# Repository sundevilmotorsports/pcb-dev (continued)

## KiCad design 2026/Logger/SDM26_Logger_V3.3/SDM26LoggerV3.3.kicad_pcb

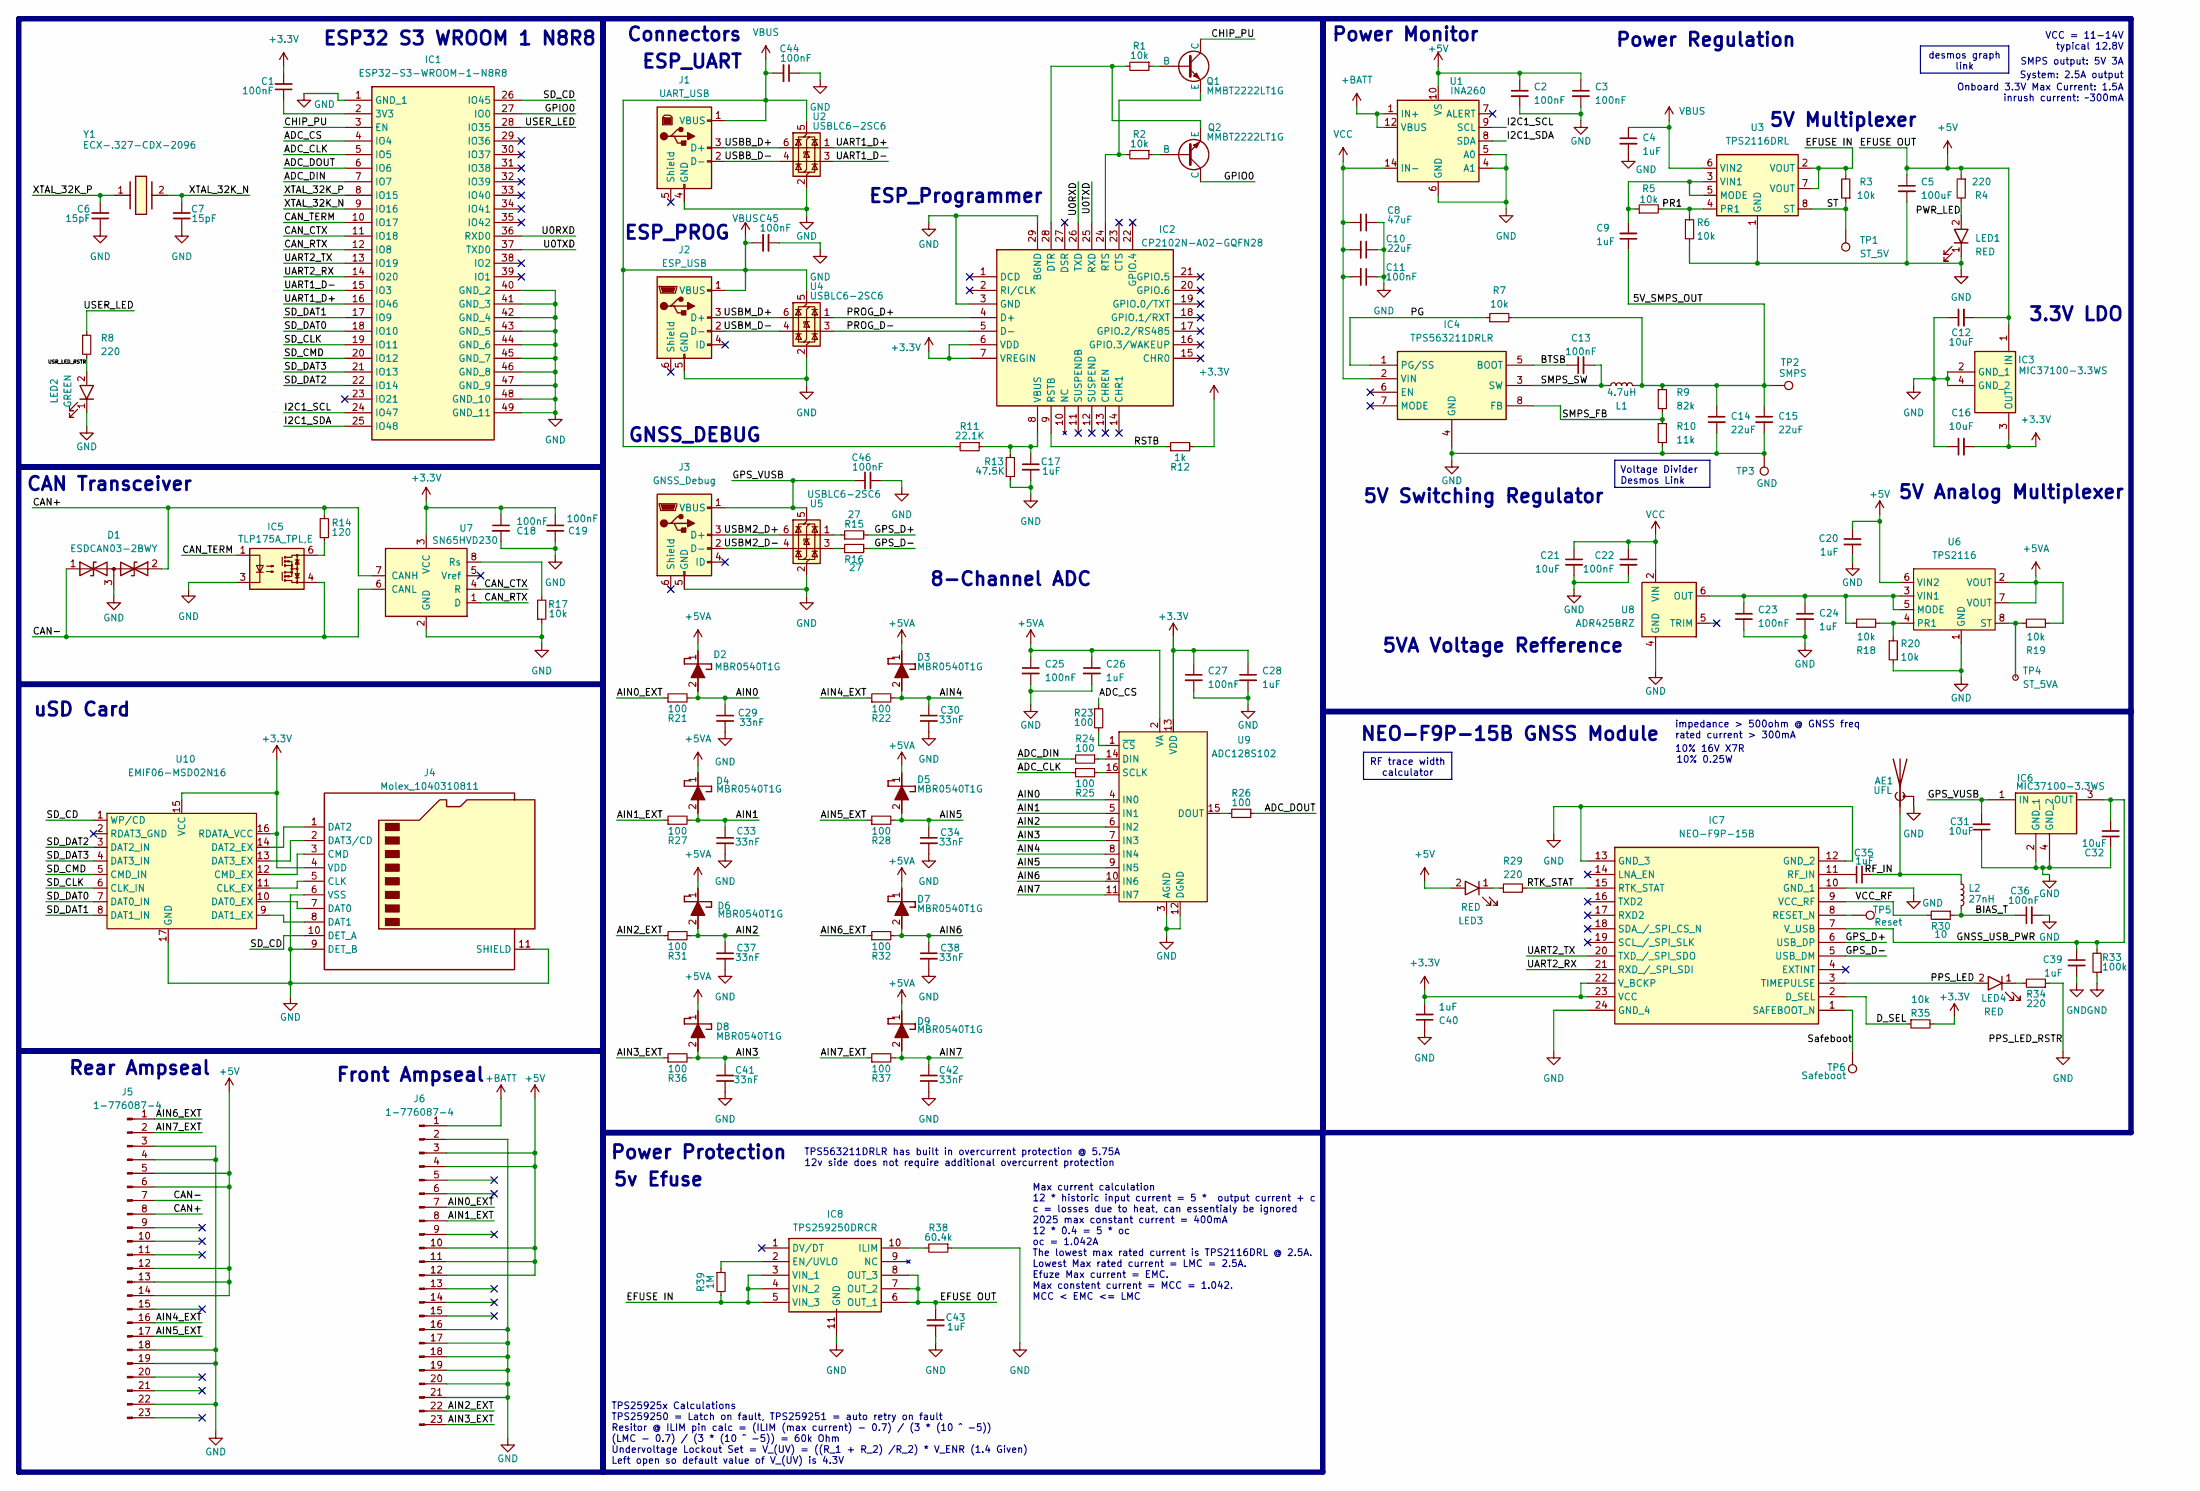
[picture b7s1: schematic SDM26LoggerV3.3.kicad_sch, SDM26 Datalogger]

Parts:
AE1: UFL; U.FL_Molex_MCRF_73412-0110_Vertical
C1, C2, C3, C11, C13, C18, C19, C22, C23, C25, C27, C36, C44, C45, C46: 100nF; C_0603_1608Metric
C4, C9, C17, C20, C24, C26, C28, C35, C39, C40, C43: 1uF; C_0603_1608Metric
C5: 100uF; CP_Elec_6.3x5.9
C6, C7: 15pF; C_0603_1608Metric
C8: 47uF; CP_Elec_6.3x5.9
C10, C14, C15: 22uF; C_0603_1608Metric
C12, C16, C21, C31, C32: 10uF; C_0603_1608Metric
C29, C30, C33, C34, C37, C38, C41, C42: 33nF; C_0603_1608Metric
D1: ESDCAN03-2BWY; SOT65P210X110-3N; Mouser Part Number 511-ESDCAN03-2BWY
D2, D3, D4, D5, D6, D7, D8, D9: MBR0540T1G; SOD3716X135N; Mouser Part Number 863-MBR0540T1G
IC1: ESP32-S3-WROOM-1-N8R8; ESP32S3WROOM1N8R8; Mouser Part Number 356-EP32S3WROOM1N8R8
IC2: CP2102N-A02-GQFN28; QFN50P500X500X80-29N-D; Mouser Part Number 634-CP2102NA02GQFN28
IC3, IC6: MIC37100-3.3WS; SOT230P700X180-4N; Mouser Part Number 998-MIC37100-3.3WS
IC4: TPS563211DRLR; SOTFL50P160X60-8N; Mouser Part Number 595-TPS563211DRLR
IC5: TLP175A_TPL,E; TLP266J; Mouser Part Number 757-TLP175A(TPLE
IC7: NEO-F9P-15B; NEOF9P15B; Mouser Part Number 377-NEO-F9P-15B
IC8: TPS259250DRCR; SON50P300X300X100-11L-D; Mouser Part Number 595-TPS259250DRCR
J1: UART_USB; 67068-7041
J2: ESP_USB; USB_Micro-B_Molex-105017-0001
J3: GNSS_Debug; USB_Micro-B_Molex-105017-0001
J4: Molex_1040310811; microSD_HC_Molex_104031-0811
J5, J6: 1-776087-4; CONN23_776087_TEC
L1: 4.7uH; L_Bourns_SRP7028A_7.3x6.6mm
L2: 27nH; L_0402_1005Metric
LED1, LED3, LED4: RED; SSFLXH100LID01; Mouser Part Number 696-SSFLXH100LID01
LED2: GREEN; SSFLXH100LID01; Mouser Part Number 696-SSFLXH100LID01
Q1, Q2: MMBT2222LT1G; SOT96P237X111-3N
R1, R2, R3, R5, R6, R7, R17, R18, R19, R20, R35: 10k; R_0603_1608Metric
R4, R8, R29, R34: 220; R_0603_1608Metric
R9: 82k; R_0603_1608Metric
R10: 11k; R_0603_1608Metric
R11: 22.1K; R_0603_1608Metric
R12: 1k; R_0603_1608Metric
R13: 47.5K; R_0603_1608Metric
R14: 120; R_0603_1608Metric
R15, R16: 27; R_0603_1608Metric
R21, R22, R23, R24, R25, R26, R27, R28, R31, R32, R36, R37: 100; R_0603_1608Metric
R30: 10; R_0603_1608Metric
R33: 100k; R_0603_1608Metric
R38: 60.4k; R_0603_1608Metric
R39: 1M; R_0603_1608Metric
TP1: ST_5V; TestPoint_Pad_1.5x1.5mm
TP2: SMPS; TestPoint_Pad_1.5x1.5mm
TP3: GND; TestPoint_Pad_1.5x1.5mm
TP4: ST_5VA; TestPoint_Pad_1.5x1.5mm
TP5: Reset; TestPoint_Pad_1.5x1.5mm
TP6: Safeboot; TestPoint_Pad_1.5x1.5mm
U1: INA260; TSSOP-16_4.4x5mm_P0.65mm
U2, U4, U5: USBLC6-2SC6; SOT-23-6
U3: TPS2116DRL; SOT-583-8
U6: TPS2116; SOT-5X3
U7: SN65HVD230; SOIC-8_3.9x4.9mm_P1.27mm
U8: ADR425BRZ; SOIC-8_3.9x4.9mm_P1.27mm
U9: ADC128S102; TSSOP-16_4.4x5mm_P0.65mm
U10: EMIF06-MSD02N16; UQFN-17-3.5x1.2mm
Y1: ECX-.327-CDX-2096; ECX327CDX2096; Mouser Part Number 520-X-.327-CDX2096

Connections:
+5V: C2.1, C3.1, C5.1, C12.2, C20.1, C43.1, IC3.1 (IN), IC8.6 (OUT_1), IC8.7 (OUT_2), IC8.8 (OUT_3), J5.5, J5.6, J5.12, J5.13, J5.14, J6.3, J6.4, J6.10, J6.11, J6.12, LED3.2 (A), R4.1, U1.10 (VS), U6.6 (VIN2)
+5VA: C25.1, C26.1, D2.1 (K), D3.1 (K), D4.1 (K), D5.1 (K), D6.1 (K), D7.1 (K), D8.1 (K), D9.1 (K), R19.2, U6.2 (VOUT), U6.7 (VOUT), U9.2 (VA)
+BATT: J6.1, U1.1 (IN+), U1.2 (IN+), U1.3 (IN+), U1.12 (VBUS)
/5V_SMPS_OUT: C9.1, C14.1, C15.1, L1.1, R7.2, R9.1, TP2.1
/ADC_CLK: IC1.5 (IO5), R25.1
/ADC_CS: IC1.4 (IO4), R23.1
/ADC_DIN: IC1.7 (IO7), R24.2
/ADC_DOUT: IC1.6 (IO6), R26.1
/AIN0: C29.1, D2.2 (A), R21.2, U9.4 (IN0)
/AIN0_EXT: J6.7, R21.1
/AIN1: C33.1, D4.2 (A), R27.2, U9.5 (IN1)
/AIN1_EXT: J6.8, R27.1
/AIN2: C37.1, D6.2 (A), R31.2, U9.6 (IN2)
/AIN2_EXT: J6.22, R31.1
/AIN3: C41.1, D8.2 (A), R36.2, U9.7 (IN3)
/AIN3_EXT: J6.23, R36.1
/AIN4: C30.1, D3.2 (A), R22.2, U9.8 (IN4)
/AIN4_EXT: J5.16, R22.1
/AIN5: C34.1, D5.2 (A), R28.2, U9.9 (IN5)
/AIN5_EXT: J5.17, R28.1
/AIN6: C38.1, D7.2 (A), R32.2, U9.10 (IN6)
/AIN6_EXT: J5.1, R32.1
/AIN7: C42.1, D9.2 (A), R37.2, U9.11 (IN7)
/AIN7_EXT: J5.2, R37.1
/BIAS_T: C36.1, L2.2, R30.1
/BTSB: C13.1, IC4.5 (BOOT)
/CAN+: D1.2, J5.8, R14.2, U7.7 (CANH)
/CAN-: D1.1, IC5.4, J5.7, U7.6 (CANL)
/CAN_CTX: IC1.11 (IO18), U7.4 (R)
/CAN_RTX: IC1.12 (IO8), U7.1 (D)
/CAN_TERM: IC1.10 (IO17), IC5.1
/CHIP_PU: IC1.3 (EN), Q1.1 (C)
/D_SEL: IC7.2 (D_SEL), R35.1
/EFUSE IN: IC8.3 (VIN_1), IC8.4 (VIN_2), IC8.5 (VIN_3), R3.2, R39.2, U3.2 (VOUT), U3.7 (VOUT)
/GNSS_USB_PWR: C32.1, C39.1, IC6.3 (OUT), IC7.7 (V_USB), R33.2
/GPIO0: IC1.27 (IO0), Q2.1 (C)
/GPS_D+: IC7.6 (USB_DP), R15.2
/GPS_D-: IC7.5 (USB_DM), R16.1
/GPS_VUSB: C31.2, C46.2, IC6.1 (IN), J3.1 (VBUS), U5.5 (VBUS)
/I2C1_SCL: IC1.24 (IO47), U1.9 (SCL)
/I2C1_SDA: IC1.25 (IO48), U1.8 (SDA)
/PG: IC4.1 (PG/SS), R7.1
/PPS_LED: IC7.3 (TIMEPULSE), LED4.2 (A)
/PR1: R5.2, R6.1, U3.4 (PR1)
/PROG_D+: IC2.4 (D+), U4.1 (I/O1)
/PROG_D-: IC2.5 (D-), U4.3 (I/O2)
/PWR_LED: LED1.2 (A), R4.2
/RF_IN: AE1.1 (A), C35.2, L2.1
/RSTB: IC2.9 (RSTB), R12.1
/RTK_STAT: IC7.15 (RTK_STAT), R29.2
/SD_CD: IC1.26 (IO45), J4.10 (DET_A), U10.1 (WP/CD)
/SD_CLK: IC1.19 (IO11), U10.6 (CLK_IN)
/SD_CMD: IC1.20 (IO12), U10.5 (CMD_IN)
/SD_DAT0: IC1.18 (IO10), U10.7 (DAT0_IN)
/SD_DAT1: IC1.17 (IO9), U10.8 (DAT1_IN)
/SD_DAT2: IC1.22 (IO14), U10.3 (DAT2_IN)
/SD_DAT3: IC1.21 (IO13), U10.4 (DAT3_IN)
/SMPS_FB: IC4.8 (FB), R9.2, R10.1
/SMPS_SW: C13.2, IC4.3 (SW), L1.2
/ST: R3.1, TP1.1, U3.8 (ST)
/Safeboot: IC7.1 (SAFEBOOT_N), TP6.1
/U0RXD: IC1.36 (RXD0), IC2.26 (TXD)
/U0TXD: IC1.37 (TXD0), IC2.25 (RXD)
/UART1_D+: IC1.16 (IO46), U2.1 (I/O1)
/UART1_D-: IC1.15 (IO3), U2.3 (I/O2)
/UART2_RX: IC1.14 (IO20), IC7.21 (RXD_/_SPI_SDI)
/UART2_TX: IC1.13 (IO19), IC7.20 (TXD_/_SPI_SDO)
/USBB_D+: J1.3 (D+), U2.6 (I/O1)
/USBB_D-: J1.2 (D-), U2.4 (I/O2)
/USBM2_D+: J3.3 (D+), U5.6 (I/O1)
/USBM2_D-: J3.2 (D-), U5.4 (I/O2)
/USBM_D+: J2.3 (D+), U4.6 (I/O1)
/USBM_D-: J2.2 (D-), U4.4 (I/O2)
/USER_LED: IC1.28 (IO35), R8.1
/USR_LED_RSTR: LED2.2 (A), R8.2
/VCC_RF: IC7.9 (VCC_RF), R30.2
/XTAL_32K_N: C7.2, IC1.9 (IO16), Y1.2
/XTAL_32K_P: C6.2, IC1.8 (IO15), Y1.1
GND: AE1.2 (Shield), C2.2, C3.2, C4.2, C5.2, C6.1, C7.1, C8.1, C10.1, C11.1, C12.1, C14.2, C15.2, C16.1, C17.2, C18.2, C19.2, C20.2, C21.2, C22.2, C23.2, C24.2, C25.2, C26.2, C27.2, C28.2, C29.2, C30.2, C31.1, C32.2, C33.2, C34.2, C36.2, C37.2, C38.2, C39.2, C40.1, C41.2, C42.2, C43.2, C44.1, C45.1, C46.1, D1.3, IC1.1 (GND_1), IC1.40 (GND_2), IC1.41 (GND_3), IC1.42 (GND_4), IC1.43 (GND_5), IC1.44 (GND_6), IC1.45 (GND_7), IC1.46 (GND_8), IC1.47 (GND_9), IC1.48 (GND_10), IC1.49 (GND_11), IC2.3 (GND), IC2.29 (BGND), IC3.2 (GND_1), IC3.4 (GND_2), IC4.4 (GND), IC5.3, IC6.2 (GND_1), IC6.4 (GND_2), IC7.10 (GND_1), IC7.12 (GND_2), IC7.13 (GND_3), IC7.24 (GND_4), IC8.11 (GND), J1.4 (GND), J2.5 (GND), J3.5 (GND), J4.6 (VSS), J4.9 (DET_B), J4.11 (SHIELD), J5.3, J5.4, J5.18, J5.19, J5.22, J6.2, J6.16, J6.17, J6.18, J6.19, J6.20, J6.21, LED1.1 (K), LED2.1 (K), R6.2, R10.2, R13.2, R17.1, R20.2, R33.1, R34.1, R38.1, TP3.1, U1.4 (A1), U1.5 (A0), U1.6 (GND), U1.11 (GND), U2.2 (GND), U3.1 (GND), U4.2 (GND), U5.2 (GND), U6.1 (GND), U7.2 (GND), U8.4 (GND), U9.3 (AGND), U9.12 (DGND), U10.17 (GND)
unnamed: IC2.28 (DTR), Q2.3 (E), R1.2
unnamed: IC2.24 (RTS), Q1.3 (E), R2.2
unnamed: C17.1, IC2.8 (VBUS), R11.1, R13.1
unnamed: IC5.6, R14.1
unnamed: IC7.8 (RESET_N), TP5.1
unnamed: C35.1, IC7.11 (RF_IN)
unnamed: IC8.2 (EN/UVLO), R39.1
unnamed: IC8.10 (ILIM), R38.2
unnamed: J4.5 (CLK), U10.11 (CLK_EX)
unnamed: J4.3 (CMD), U10.12 (CMD_EX)
unnamed: J4.7 (DAT0), U10.10 (DAT0_EX)
unnamed: J4.8 (DAT1), U10.9 (DAT1_EX)
unnamed: J4.1 (DAT2), U10.14 (DAT2_EX)
unnamed: J4.2 (DAT3/CD), U10.13 (DAT3_EX)
unnamed: LED3.1 (K), R29.1
unnamed: LED4.1 (K), R34.2
unnamed: Q1.2 (B), R1.1
unnamed: Q2.2 (B), R2.1
unnamed: R15.1, U5.1 (I/O1)
unnamed: R16.2, U5.3 (I/O2)
unnamed: C9.2, R5.1, U3.3 (VIN1), U3.5 (MODE)
unnamed: C23.1, C24.1, R18.1, U6.3 (VIN1), U6.5 (MODE), U8.6 (OUT)
unnamed: R18.2, R20.1, U6.4 (PR1)
unnamed: R19.1, TP4.1, U6.8 (ST)
unnamed: R17.2, U7.8 (Rs)
unnamed: R24.1, U9.14 (DIN)
unnamed: R26.2, U9.15 (DOUT)
unnamed: R25.2, U9.16 (SCLK)
unnamed: R23.2, U9.1 (~CS)
VBUS: C4.1, C44.2, C45.2, J1.1 (VBUS), J2.1 (VBUS), R11.2, U2.5 (VBUS), U3.6 (VIN2), U4.5 (VBUS)
VCC: C8.2, C10.2, C11.2, C21.1, C22.1, IC4.2 (VIN), U1.14 (IN-), U1.15 (IN-), U1.16 (IN-), U8.2 (VIN)

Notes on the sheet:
Power Regulation
5V Multiplexer
CAN Transceiver
10% 16V X7R
5v Efuse
inrush current: ~300mA
5V Switching Regulator
5V Analog Multiplexer
ESP32 S3 WROOM 1 N8R8
Power Monitor
Connectors
10% 0.25W
ESP_PROG
Onboard 3.3V Max Current: 1.5A
impedance > 500ohm @ GNSS freq rated current > 300mA
Front Ampseal
3.3V LDO
VCC = 11-14V typical 12.8V
GNSS_DEBUG
Max current calculation 12 * historic input current = 5 * output current + c c = losses due to heat, can essentialy be ignored 2025 max constant current = 400mA 12 * 0.4 = 5 * oc oc = 1.042A The lowest max rated current is TPS2116DRL @ 2.5A. Lowest Max rated current = LMC = 2.5A. Efuze Max current 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
ESP_UART
TPS563211DRLR has built in overcurrent protection @ 5.75A 12v side does not require additional overcurrent protection
8-Channel ADC
uSD Card
ESP_Programmer
Power Protection
5VA Voltage Refference
SMPS output: 5V 3A
NEO-F9P-15B GNSS Module
System: 2.5A output
Rear Ampseal
TPS25925x Calculations TPS259250 = Latch on fault, TPS259251 = auto retry on fault Resitor @ ILIM pin calc = (ILIM (max current) - 0.7) / (3 * (10 ^ -5)) (LMC - 0.7) / (3 * (10 ^ -5)) = 60k Ohm Undervoltage Lockout Set = V_(UV) = ((R_1 + R_2) /R_2) * V_ENR (1.4 Given) Left open so default value of 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
desmos graph link
Voltage Divider Desmos Link
RF trace width calculator

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
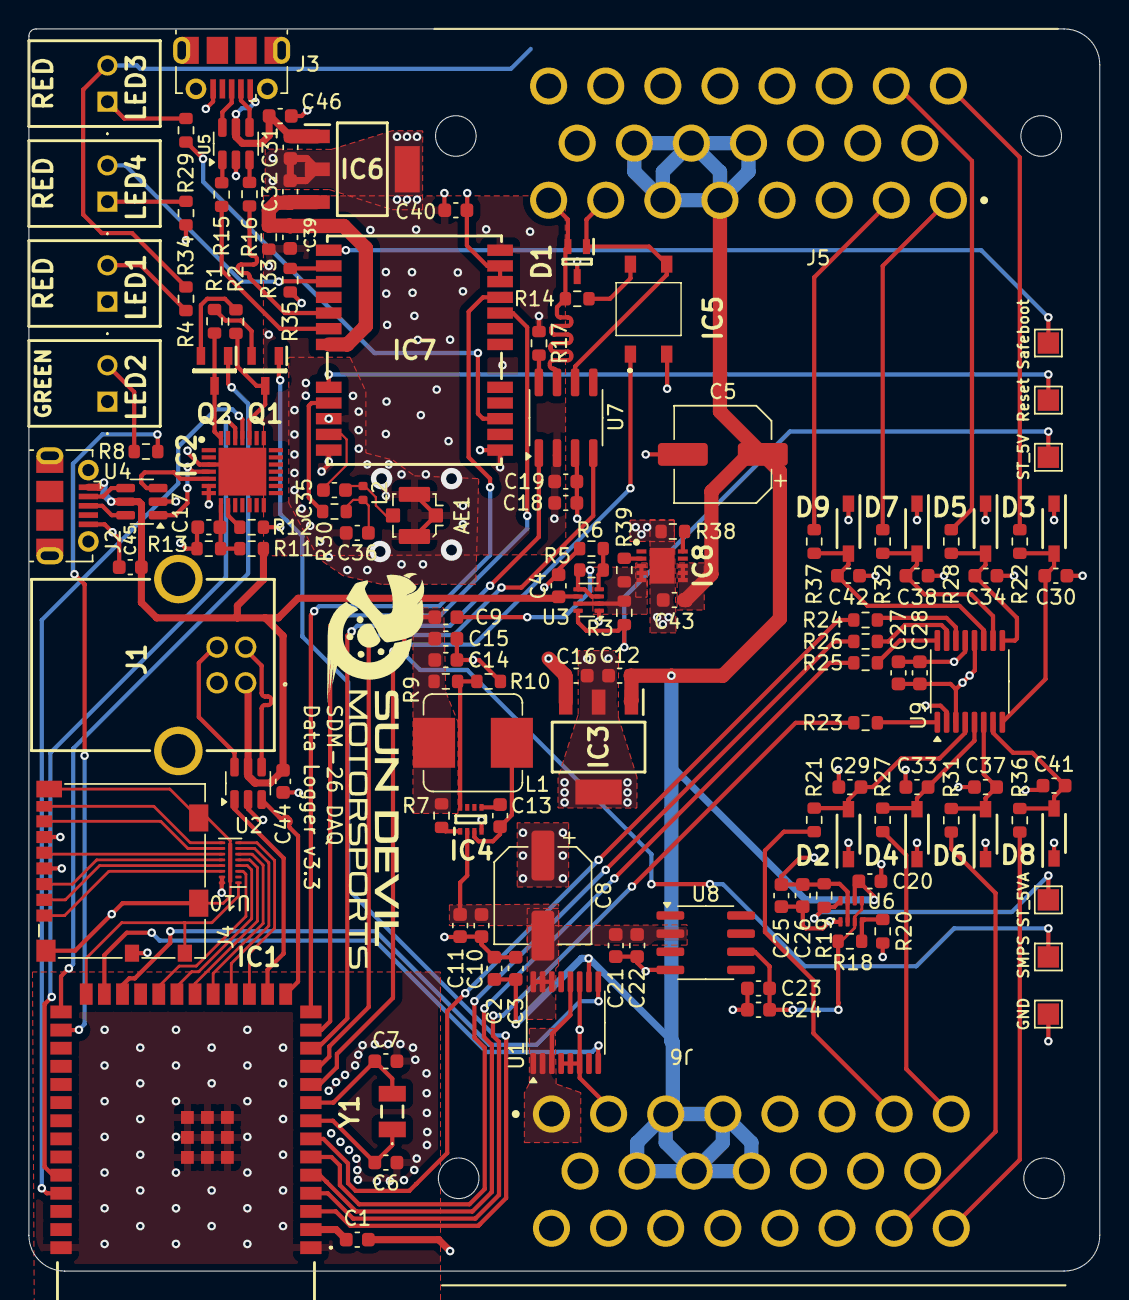
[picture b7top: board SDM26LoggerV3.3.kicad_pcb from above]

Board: 4 copper layers, 75.0 x 87.0 mm, 134 parts (0 on the bottom side), 112 nets.

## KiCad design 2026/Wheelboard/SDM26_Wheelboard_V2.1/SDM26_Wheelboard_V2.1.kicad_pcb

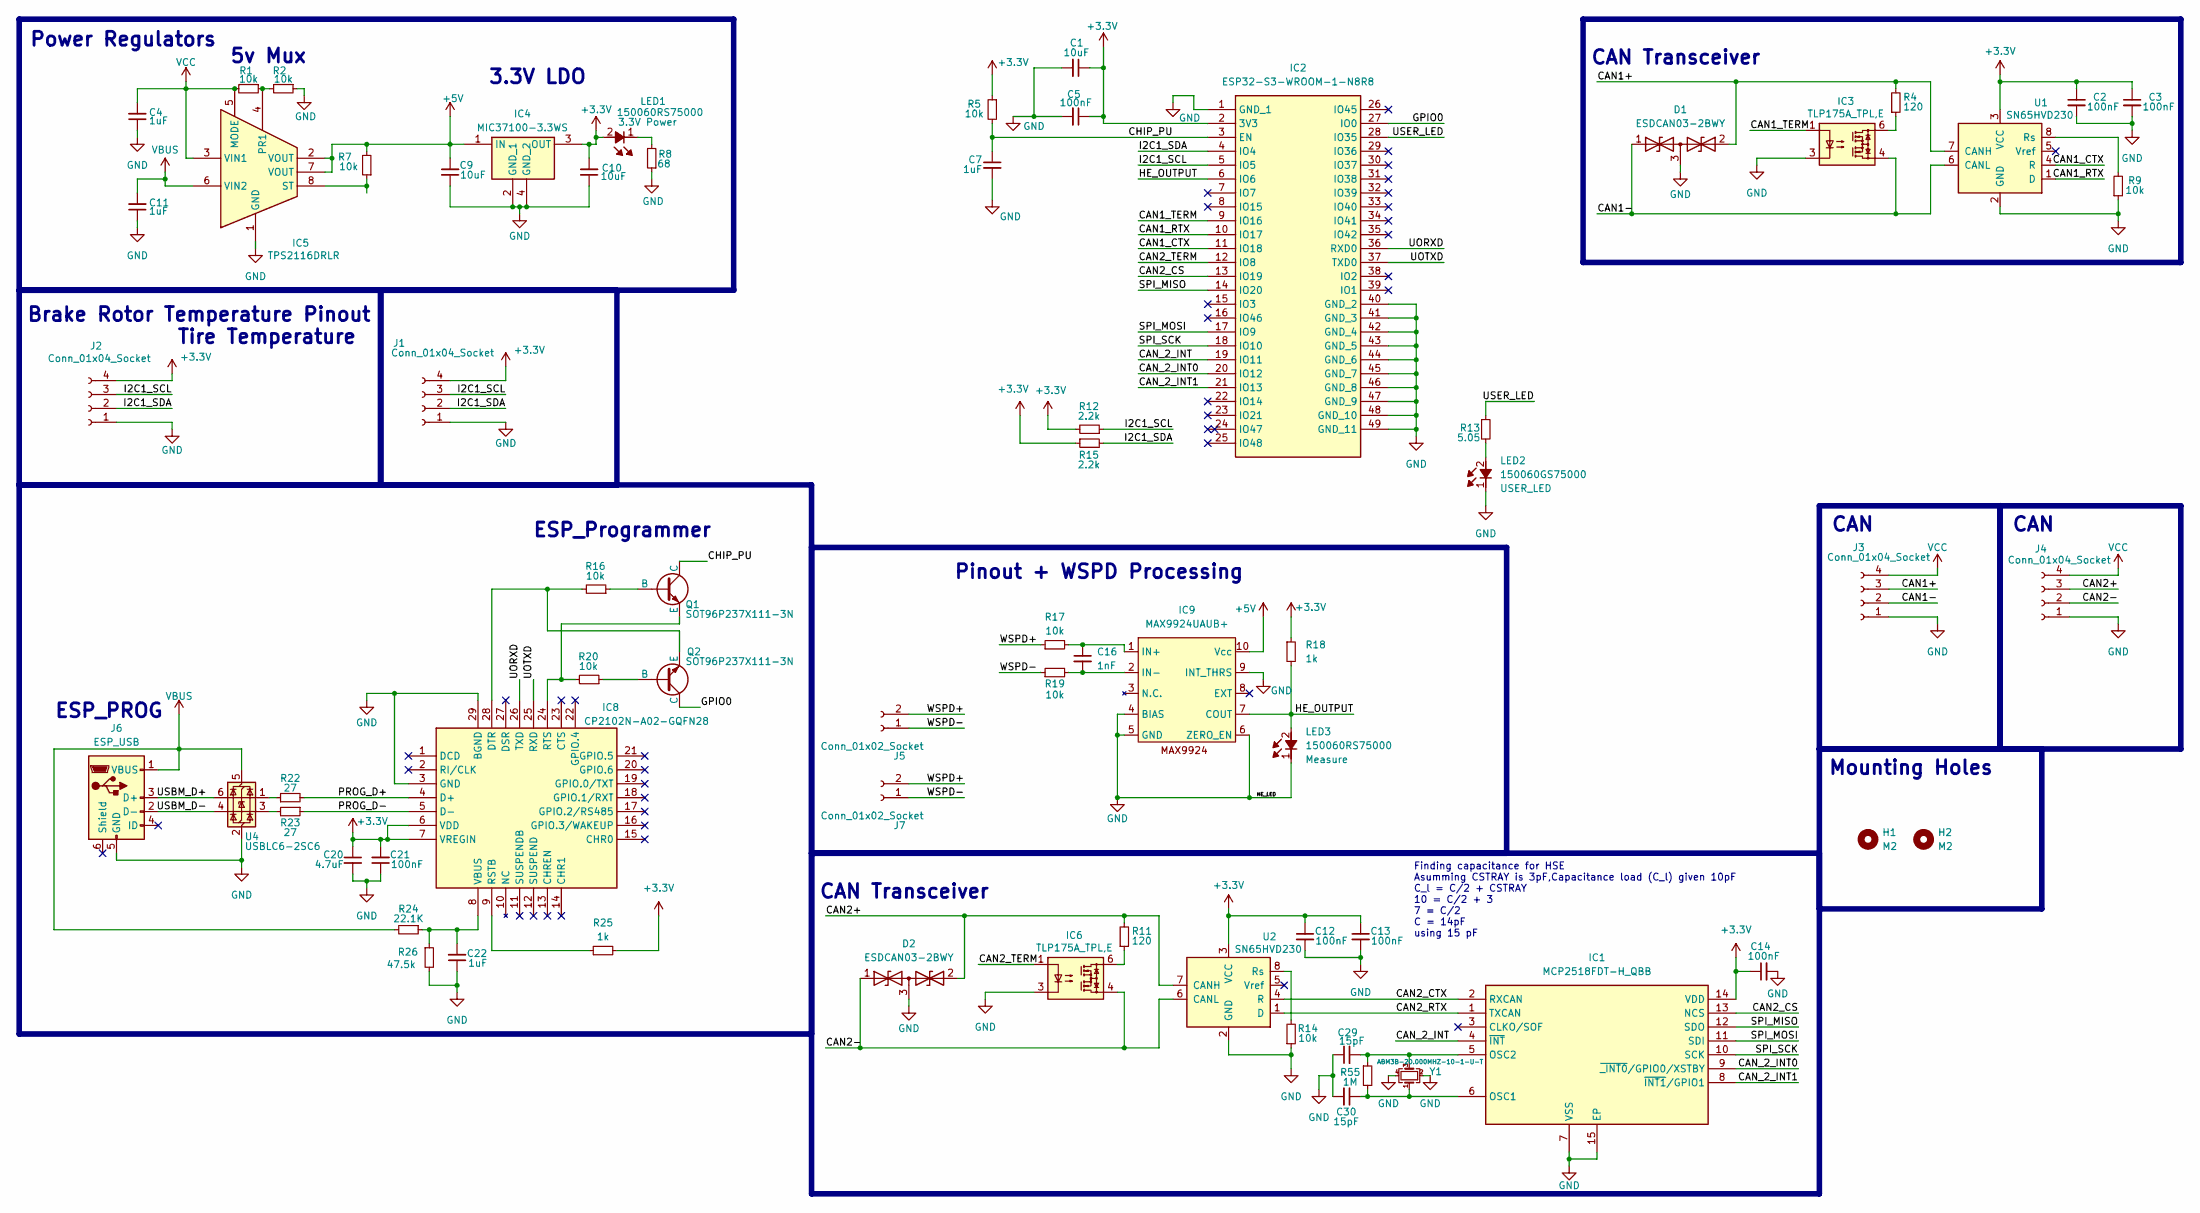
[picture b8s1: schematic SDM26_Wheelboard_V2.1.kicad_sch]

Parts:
C1, C9, C10: 10uF; C_0603_1608Metric
C2, C3, C5, C12, C13, C14, C21: 100nF; C_0603_1608Metric
C4, C7, C11, C22: 1uF; C_0603_1608Metric
C16: 1nF; C_0603_1608Metric
C20: 4.7uF; C_0603_1608Metric
C29, C30: 15pF; C_0603_1608Metric
D1, D2: ESDCAN03-2BWY; SOT65P210X110-3N; Mouser Part Number 511-ESDCAN03-2BWY
H1, H2: M2; MountingHole_3.2mm_M3
IC1: MCP2518FDT-H_QBB; SON65P300X450X90-15L-D; Mouser Part Number 579-MCP2518FDT-H/QBB
IC2: ESP32-S3-WROOM-1-N8R8; ESP32S3WROOM1N8R8; Mouser Part Number 356-EP32S3WROOM1N8R8
IC3, IC6: TLP175A_TPL,E; TLP266J; Mouser Part Number 757-TLP175A(TPLE
IC4: MIC37100-3.3WS; SOT230P700X180-4N; Mouser Part Number 998-MIC37100-3.3WS
IC5: TPS2116DRLR; SOTFL50P160X60-8L; Mouser Part Number 595-TPS2116DRLR
IC8: CP2102N-A02-GQFN28; QFN50P500X500X80-29N-D; Mouser Part Number 634-CP2102NA02GQFN28
IC9: MAX9924UAUB+; SOP50P490X110-10L; Mouser Part Number 700-MAX9924UAUB
J1, J2, J3, J4: Conn_01x04_Socket; JST_XH_S4B-XH-A_1x04_P2.50mm_Horizontal
J5, J7: Conn_01x02_Socket; JST_XH_S2B-XH-A_1x02_P2.50mm_Horizontal
J6: ESP_USB; USB_Micro-B_Molex-105017-0001
LED1, LED3: 150060RS75000; LEDC1608X80N; Mouser Part Number 710-150060RS75000
LED2: 150060GS75000; LEDC1608X80N; Mouser Part Number 710-150060VS75000
Q1, Q2: SOT96P237X111-3N
R1, R2, R5, R7, R9, R14, R16, R17, R19, R20: 10k; R_0603_1608Metric
R4, R11: 120; R_0603_1608Metric
R8: 68; R_0603_1608Metric
R12, R15: 2.2k; R_0603_1608Metric
R13: 5.05; R_0603_1608Metric
R18, R25: 1k; R_0603_1608Metric
R22, R23: 27; R_0603_1608Metric
R24: 22.1K; R_0603_1608Metric
R26: 47.5k; R_0603_1608Metric
R55: 1M; R_0603_1608Metric
U1, U2: SN65HVD230; SOIC-8_3.9x4.9mm_P1.27mm
U4: USBLC6-2SC6; SOT-23-6
Y1: ABM3B-20.000MHZ-10-1-U-T; ABM3B; Mouser Part Number 815-ABM3B-20-T

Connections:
+3.3V: C1.1, C2.1, C3.1, C5.1, C10.2, C12.1, C13.1, C14.1, C20.1, C21.2, IC1.14 (VDD), IC2.2 (3V3), IC4.3 (OUT), IC8.6 (VDD), IC8.7 (VREGIN), J1.4, J2.4, LED1.2 (A), R5.1, R12.2, R15.1, R18.1, R25.2, U1.3 (VCC), U2.3 (VCC)
+5V: C9.2, IC4.1 (IN), IC5.2 (VOUT), IC5.7 (VOUT), IC9.10 (Vcc), R7.2
/CAN1+: D1.2, J3.3, R4.2, U1.7 (CANH)
/CAN1-: D1.1, IC3.4, J3.2, U1.6 (CANL)
/CAN1_CTX: IC2.11 (IO18), U1.4 (R)
/CAN1_RTX: IC2.10 (IO17), U1.1 (D)
/CAN1_TERM: IC2.9 (IO16), IC3.1
/CAN2+: D2.2, J4.3, R11.2, U2.7 (CANH)
/CAN2-: D2.1, IC6.4, J4.2, U2.6 (CANL)
/CAN2_CS: IC1.13 (NCS), IC2.13 (IO19)
/CAN2_CTX: IC1.2 (RXCAN), U2.4 (R)
/CAN2_RTX: IC1.1 (TXCAN), U2.1 (D)
/CAN2_TERM: IC2.12 (IO8), IC6.1
/CAN_2_INT: IC1.4 (~INT), IC2.19 (IO11)
/CAN_2_INT0: IC1.9 (~_INT0/GPIO0/XSTBY), IC2.20 (IO12)
/CAN_2_INT1: IC1.8 (~INT1/GPIO1), IC2.21 (IO13)
/CHIP_PU: C7.1, IC2.3 (EN), Q1.1 (C), R5.2
/GPIO0: IC2.27 (IO0), Q2.1 (C)
/HE_OUTPUT: IC2.6 (IO6), IC9.7 (COUT), LED3.2 (A), R18.2
/I2C1_SCL: IC2.5 (IO5), J1.3, J2.3, R12.1
/I2C1_SDA: IC2.4 (IO4), J1.2, J2.2, R15.2
/PROG_D+: IC8.4 (D+), R22.2
/PROG_D-: IC8.5 (D-), R23.1
/SPI_MISO: IC1.12 (SDO), IC2.14 (IO20)
/SPI_MOSI: IC1.11 (SDI), IC2.17 (IO9)
/SPI_SCK: IC1.10 (SCK), IC2.18 (IO10)
/UORXD: IC2.36 (RXD0), IC8.26 (TXD)
/UOTXD: IC2.37 (TXD0), IC8.25 (RXD)
/USBM_D+: J6.3 (D+), U4.6 (I/O1)
/USBM_D-: J6.2 (D-), U4.4 (I/O2)
/USER_LED: IC2.28 (IO35), R13.1
/WSPD+: J5.2, J7.2, R17.1
/WSPD-: J5.1, J7.1, R19.1
GND: C1.2, C2.2, C3.2, C4.1, C5.2, C7.2, C9.1, C10.1, C11.1, C12.2, C13.2, C14.2, C20.2, C21.1, C22.1, C29.1, C30.2, D1.3, D2.3, IC1.7 (VSS), IC1.15 (EP), IC2.1 (GND_1), IC2.40 (GND_2), IC2.41 (GND_3), IC2.42 (GND_4), IC2.43 (GND_5), IC2.44 (GND_6), IC2.45 (GND_7), IC2.46 (GND_8), IC2.47 (GND_9), IC2.48 (GND_10), IC2.49 (GND_11), IC3.3, IC4.2 (GND_1), IC4.4 (GND_2), IC5.1 (GND), IC6.3, IC8.3 (GND), IC8.29 (BGND), IC9.4 (BIAS), IC9.5 (GND), IC9.6 (ZERO_EN), IC9.9 (INT_THRS), J1.1, J2.1, J3.1, J4.1, J6.5 (GND), LED2.1 (K), LED3.1 (K), R2.1, R8.1, R9.1, R14.1, R26.2, U1.2 (GND), U2.2 (GND), U4.2 (GND), Y1.2 (GND_1), Y1.4 (GND_2)
unnamed: C30.1, IC1.6 (OSC1), R55.2, Y1.1 (XTAL_1)
unnamed: C29.2, IC1.5 (OSC2), R55.1, Y1.3 (XTAL_2)
unnamed: IC3.6, R4.1
unnamed: IC5.4 (PR1), R1.1, R2.2
unnamed: IC5.8 (ST), R7.1
unnamed: IC6.6, R11.1
unnamed: IC8.28 (DTR), Q2.3 (E), R16.2
unnamed: IC8.9 (RSTB), R25.1
unnamed: IC8.24 (RTS), Q1.3 (E), R20.2
unnamed: C22.2, IC8.8 (VBUS), R24.1, R26.1
unnamed: C16.1, IC9.1 (IN+), R17.2
unnamed: C16.2, IC9.2 (IN-), R19.2
unnamed: LED1.1 (K), R8.2
unnamed: LED2.2 (A), R13.2
unnamed: Q1.2 (B), R16.1
unnamed: Q2.2 (B), R20.1
unnamed: R22.1, U4.1 (I/O1)
unnamed: R23.2, U4.3 (I/O2)
unnamed: R9.2, U1.8 (Rs)
unnamed: R14.2, U2.8 (Rs)
VBUS: C11.2, IC5.6 (VIN2), J6.1 (VBUS), R24.2, U4.5 (VBUS)
VCC: C4.2, IC5.3 (VIN1), IC5.5 (MODE), J3.4, J4.4, R1.2

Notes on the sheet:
3.3V LDO
Brake Rotor Temperature Pinout
Tire Temperature
5v Mux
ESP_Programmer
CAN
CAN Transceiver
Mounting Holes
ESP_PROG
Power Regulators
Pinout + WSPD Processing
Finding capacitance for HSE Asumming CSTRAY is 3pF,Capacitance load (C_l) given 10pF C_l = C/2 + CSTRAY 10 = C/2 + 3 7 = C/2 C = 14pF using 15 pF

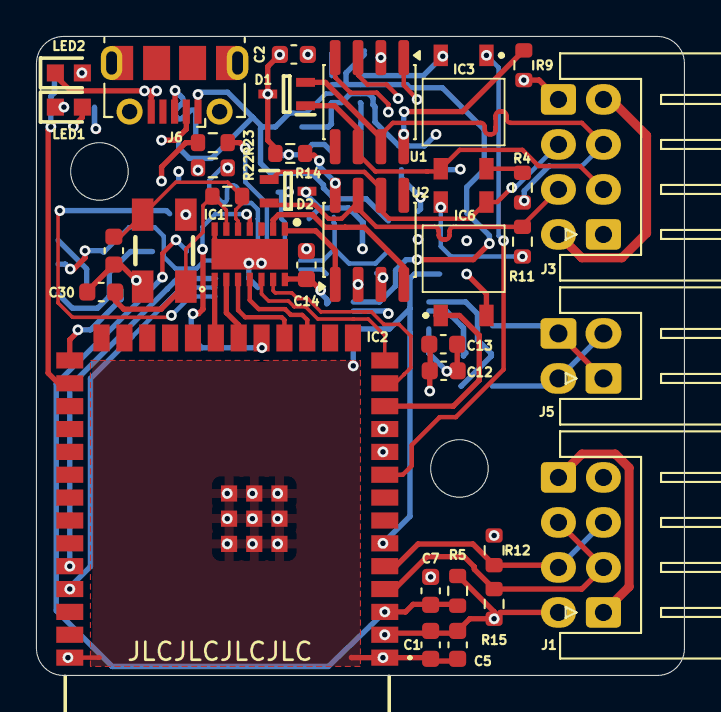
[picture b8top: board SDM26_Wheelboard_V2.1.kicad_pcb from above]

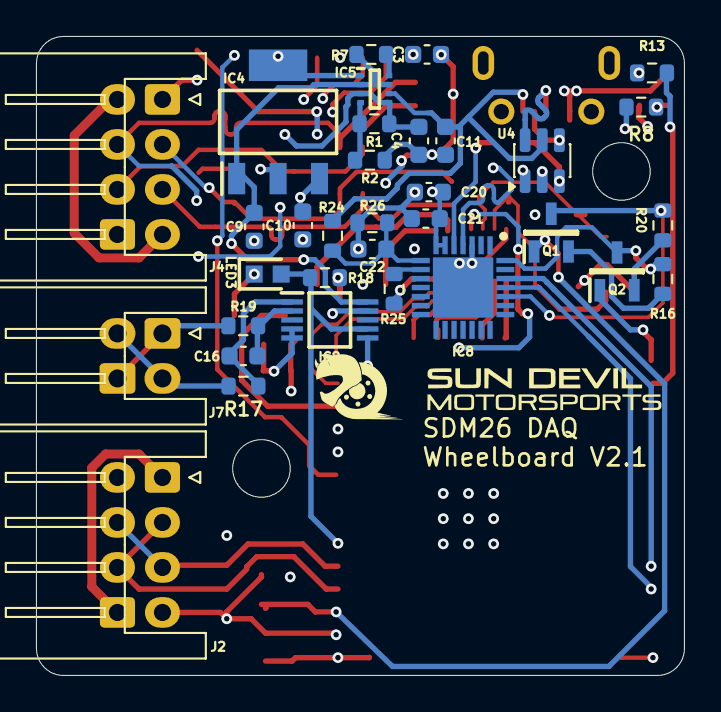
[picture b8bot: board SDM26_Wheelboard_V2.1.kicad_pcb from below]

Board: 4 copper layers, 36.0 x 35.5 mm, 69 parts (34 on the bottom side), 56 nets.

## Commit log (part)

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2023-10-19 optocoupler for drs button
2023-10-20 planning for external adc
2023-10-20 adding externl adc
2023-10-21 adding model for i2c shifter
2023-10-21 uploading
2023-10-23 wheel speed board first iteration
2023-10-23 wheel board updates
2023-10-23 ADC pinouts
2023-10-26 uploading changes
2023-10-26 add footprints for volt ref
2023-10-27 length match can splitter, add adapter for load cell connector
2023-10-30 finalize wheel speed board
2023-10-31 finalize wheel board
2023-11-01 drs box started
2023-11-02 more progress on drs box
2023-11-02 update label wheel board
2023-11-04 found shifter for drs
2023-11-08 start routing on logger
2023-11-09 IMU Box PCB added
2023-11-09 Added document values to IMU Box
2023-11-10 sdio routing on data logger
2023-11-10 reorganize logger schematic
2023-11-10 git ignore lock file
2023-11-10 cleaning
2023-11-11 start working on digital i/o for logger
2023-11-12 add power monitor to data logger
2023-11-13 routed power circuitry
2023-11-14 digital input for data logger
2023-11-15 logger panel
2023-11-30 IMUBox
2023-11-30 drs board
2023-12-01 logger updates
2023-12-03 fahb files
2023-12-03 logger: move c13 to vbat
2023-12-03 logger: redo 5v routing
2023-12-03 change 5va mux input
2023-12-03 logger: adjust trace spacing
2023-12-03 logger: fix adr425 footprint
2023-12-03 logger: general improvements
2023-12-04 sent logger/wheel/he/cansplitter/lca/imu for fabrication
2023-12-05 assembly info for logger
2023-12-05 more assembly drawings
2023-12-19 panel
2024-01-14 hehez
2024-01-14 over engineering yet again
2024-01-15 finalize telemetry
2024-01-15 add led to lap receiver
2024-01-16 fix swd in wheel board
2024-01-21 data logger 3.1
2024-01-21 wheel board v1.1
2024-01-21 Fab files for pcbway
2024-01-21 adding gps connector to panel model
2024-01-22 logger panel changes
2024-01-22 adjust nrf footprint
2024-01-28 less wide logger
2024-01-28 before change to conn footprint
2024-01-28 remove mech hole for connector
2024-02-01 ordered logger v3.1, panel, shifter
2024-04-06 drawings and update can splitter with mappings
2024-08-31 SDM25 Wheelboard updates
    Incremental work - unfinished.
2024-09-17 SDM-25 Wheelboard
    Includes preliminary design for accompanying mlx-breakout board. Power delivery/input for new 5V WSPD sensor.
2024-10-03 Cansplitter revision added
    Let me know if I need to add anything
2024-10-26 Improved CANsplitter revisions
    brrr
2024-12-05 can splitter mfg
    update to include markings + output files for manufacturing
2024-12-05 STM32 telemetry upload
    includes first revision STM32 based telemetry board - by matthew mcconnell
2024-12-15 telem pcb updates
    updated labels + assignments for prod
2024-12-15 telem + cansplitter builds
    included build files sent out for manufacture
2024-12-17 wheelboard wspd revision
    first iteration using MAX9924 and VR sensor
2024-12-26 WSPD MAX9924 PCB Integration
    Integrated MAX9924 IC into the wheelboard PCB for WSPD measurement.
2025-01-23 Telemetry CAN Pin Fix
    Moved CAN pins to correct pins on STM32
2025-01-23 SDM25_IMU_STM32
    New IMU board with STM32
2025-01-23 SDM25_IMU Edits
    -Renamed components to avoid duplicate component names.
    -Other small fixes
2025-01-25 SDM25 Steering Wheel
    Bulk of steering wheel files, including files for manufacture. Most design work done by Erin Pryor.
2025-01-25 Manuf. Builds.
    Buildout for Manufacture on several boards.
2025-01-30 Last minute board fixes.
    Changed I2C pull down resistors to pull up on Telemetry and IMU.
    Improved routing of NRST pin on IMU.
2025-02-01 SDM-24 Logger TVS diodes
    TVS protection added on all analog inputs. Also built out for manufacture files.
2025-02-02 IMU + Telemetry + Steering Wheel
    Final manufacturing outputs
2025-02-03 drs/mpcm
    modified DRS with multipurpose control module labeling for SDM-25, module will be used in ARB + shiftR
2025-03-01 drs/mcpm fix
    changing folder name
    also uploading WIP steering wheel revision
2025-03-01 dwg template fix
2025-03-16 Steering Wheel REV2
    Complete overhaul of the steering wheel module complete - ready for review.
2025-03-17 Post-Feedback STW Updates
    Updates to Steering PCB regarding differential pair routing.
2025-03-17 BSPD
2025-03-18 BSPD edits
2025-03-18 BSPD edits
    Connector and LED
2025-03-19 BSPD
    ft BIG LED and the correct DT(M) Connector
2025-04-03 3/20/25 Fab Outputs
2025-04-04 IMU Fix
    Fixed CAN, I2C, and USB Differential Pairs
2025-04-04 IMU Fixes (electric boogaloo)
    further fixes
2025-04-05 IMU fix
    USB D+ D-
2025-04-05 Telemetry - CAN, I2C, USB Fix
    Fr this time
2025-04-12 BSPD
    New Latch
    New Trimmers
2025-04-12 Teensy Telemetry
2025-05-09 evan's 5/8 push
2025-05-18 Adding BSPD Circuit
2025-05-22 Beginning logger the loooong way (V3) and other misc changes
2025-05-25 Logger V3.0 wiring complete needs silkscreen fixes
2025-05-30 Logger 3.1
2025-05-30 Logger V3.11
2025-05-31 Wheelboard 2026 Commit
2025-05-31 Put into right folder
2025-06-02 Update L2 to correct size and other misc changes
2025-06-03 Small changes to schematic
2025-06-03 Added Diode and JST 4 pin automotive connector
2025-06-05 CAN Splitter
2025-06-06 update voltage divider to more common values and changed CAN termination to MOSFET
2025-06-06 Adding Optocoupler for CAN termination
2025-06-07 Updated splitter to have red LED and evenly split connectors
2025-06-09 Begin adding efuse to logger v3.3, syncing to other computer
2025-06-09 Added Efuse to logger board
2025-06-09 Made a little more pretty :3
2025-06-10 BSPD Sync
2025-06-10 Misc Changes
2025-06-10 BSPD logic and latch simulated in Falstad
2025-06-11 BSPD power regulation + Splitter format changes
2025-06-12 BSPD Schematic mostly done
2025-06-12 PSBD PCB Logic nearly done
2025-06-12 Minor fixes
2025-06-13 Computer Sync
2025-06-13 BSPD BOTTOM TEXT
2025-06-14 BSPD Misc
2025-06-15 Adding Gerber and msic
2025-06-16 Fixed AND gate output on wrong pin
2025-06-17 Changed AND gate
2025-06-17 Added power smoothing to USB Power
2025-06-18 PRE 2026 SDM PCBs
2025-06-19 PSPD Test Bench commit
2025-06-20 Naming Clarification
2025-06-25 Small BSPD Naming update
2025-07-04 misc
2025-07-04 BSPD Formatting and misc
2025-07-04 BSPD V1.1
2025-07-04 Added thermal relief on power LEDs and other misc.
2025-07-05 Cosmetics
2025-07-09 Nondimensional Schematic rev1 done
2025-07-10 NDTC BCP Start
2025-07-11 NDTC PCB mostly done
2025-07-15 Connected ground
2025-07-15 Fixed decoupling capacitor on ESP32
2025-07-15 Schematic done but needs to be double checked, PCB started
2025-07-16 NTC First Rev Complete
2025-07-17 Timing gates Schematic + PCB Done
2025-07-17 Length matched USB and added mounting holes
2025-07-19 Added silkscreen + Misc
2025-08-15 Logger 4.0 commit
2025-08-16 IMU V1.0 Commit
2025-08-16 Timing Gates 2.0 Commit
2025-08-21 IMU Ver3
    Fixed C1. Moved pull up resistors to ESP. Changed all capacitors from 100nF to 100uF. Change USER_LED to 150060GS75000 and R1 to 5.05 Ohms. Added 4.7uF and 10uF to VDD and VREGIN. Moved U0RXD to pin 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
2025-08-22 Revert "IMU Ver3"
    This reverts commit aa024b82b5cf559e973aef8b38026070112d2297.
2025-08-23 Added sensor stuff
2025-08-30 Updates Before September Order
2025-08-30 September order sync
2025-08-31 September order final commit
2025-09-01 Figures (Unhinged)
2025-09-01 Final Final update for September order
2025-09-04 Updated comparator pull-up resistor values
2025-09-06 Template Sch
2025-09-06 EDITS TO TEMPLATE SCH
2025-09-19 Create SDM26_Wheelboard_V1.2.kicad_sch
    Added some new connections to the microcontroller. I don't know how to make a while folder so apologies if this is messed up
2025-09-20 SW changer
2025-09-23 Steering Wheel Sch, and libs
    complete version of steering wheel schematic with all new parts added to libraries
2025-09-23 SW updates
2025-09-24 SW update
2025-09-25 SW LED driver updates
2025-09-26 Fixxed mux and leds and stuff
2025-09-26 Added IMU and updated naming conventions
2025-09-30 Steering wheel update
2025-09-30 Cleaning file system
2025-09-30 Wheel board update
2025-09-30 Fixed issues with template
2025-09-30 Misc Library Update
2025-10-01 SW PCB start
2025-10-02 SW PCB progress
2025-10-02 SW PCB Done
2025-10-02 SW CAD updates
2025-10-02 SW fixed so matching systems assembly
2025-10-03 SW dimension fixes
2025-10-04 Systems got me workin
2025-10-04 aint-shit-sweet
2025-10-07 Double boof
2025-10-08 Wheelboard Progress - added CAN SPI
2025-10-08 Misc libraries update
2025-10-08 Temp sensor update
2025-10-08 Adding SD card to SW
2025-10-08 Update Wheelboard dimensions again
2025-10-08 Logger misc
2025-10-08 Finished adding steering wheel uSD
2025-10-10 Edited pcb layout. Added CAN 2 circuitry
2025-10-10 Temp sensor and msic update
2025-10-17 pitot board :)
2025-10-17 Wheelboard dimesnion update
2025-10-17 Changed STEP export location
2025-10-17 CAN Splitter Mini
2025-10-18 Moved Mini edge connectors
2025-10-20 Fixed PCB for systems
2025-10-20 Fixing SW Regression
2025-10-20 Revert "Fixing SW Regression"
    This reverts commit b1f5285f4e309ac5406c286e558759261840c35c.
2025-10-20 Fixing stering wheel for systems (again?)
2025-10-20 fixed overwritten sw commit
2025-10-24 Moved around some stuff on the red side and like one thing on the blue
2025-10-31 Wheelboard AGAIN
2025-11-03 wheel board 1.3 + parts added to libraries
2025-11-08 Wheel Board 1.3
2025-11-14 Updated Output directory
2025-11-14 Changed Format
2025-11-15 Finalizing Wheelboards
2025-11-15 Fixed analog and added misc 2
2025-11-18 Misc (A lot and I don't wanna organize 😛)
2025-11-21 Nathaniel first commit added KiCad shifter project, pcb, and schematic
2025-11-21 added prl file
2025-11-25 Added Rotor Temp Sensor board
2025-11-26 Dash and ESP32 template
    Made Dash Project
    Fixed some of the footprints and made more usable
2025-11-26 Dash edits and added symbol and footprints to lib
2025-12-04 Dash and Libraries Update
2026-01-15 Naming Updates
2026-01-16 Dash Updates
2026-01-16 Renamed Variable Resistors to Potentiometers
2026-01-16 misc updates
2026-01-16 fix path for libs i hope
2026-01-17 Dash Sch Edits
    Moved to USB-C
    Progress on RGB LED nets
2026-01-18 Changed dash to IP67 USB C
2026-01-18 Wheelboard 2.1 fixed 5v power for wsp ic
2026-01-21 update ESP32S3 MCU Template
    Changed R15 from 10k to 0ohm
2026-01-22 One more fix on esp32 template sch
    chip pu
2026-01-31 Dash progress
    added to libs and swaped dash to BT818. Work in progress
2026-02-17 Timing gates V3.0
2026-02-17 SDM27 Logger
2026-02-17 Temp Sensor Board
2026-02-17 Idk shmerp
2026-02-18 NDTC Fixing pwr pin swap
2026-02-18 27 can spliter
2026-02-19 Dash PCB work
2026-02-19 Dash
2026-02-20 add telemetry
2026-02-25 SW removed display added spi connection
2026-02-25 Telemetry finalization
2026-02-25 Cleaning schematic
2026-02-27 Decreased Splitter size
2026-02-27 Added Magnetometer
2026-02-27 Fixing IMU_V1.0 getting nuked
2026-03-03 Can Splitter and mini Can Splitter updates
2026-03-03 Added RF amplifier to telemetry board
2026-03-19 Cleaning IMU Repo
2026-03-19 (Misc) Updated export locations
2026-03-19 Updated naming and small updates
2026-03-19 (Misc) Changed naming and output dir
2026-03-19 Renamed, added impedance matching documentation
2026-03-19 Renamed V3 to V2.1
2026-03-19 Changed naming conventions
2026-04-02 Hella dash edits
    just cranked that shit out
2026-04-04 Dash check, Fernando
2026-05-18 SDM27 C5 Wheel board started
    basic wip wheel board sch, with dual band RF ( :
2026-05-19 Wheel board parts update
2026-05-19 Wheel Board, new parts added
2026-05-21 more edits, board still very WIP. need to add USB
2026-06-14 Slip Angle V1
    Board done, ive got all the parts
2026-06-14 Fixed a werid trace thing on slip angle
2026-06-15 Quick Lib Update
2026-06-17 SA12 footprint part
2026-06-18 Project folders with notes
2026-06-20 Slip angle v2
2026-06-20 small fix to slip
2026-06-21 Cooling Sensor Board progres
